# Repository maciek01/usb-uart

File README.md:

# usb-uart

first prototype for usb->uart board with FTDI 232rl

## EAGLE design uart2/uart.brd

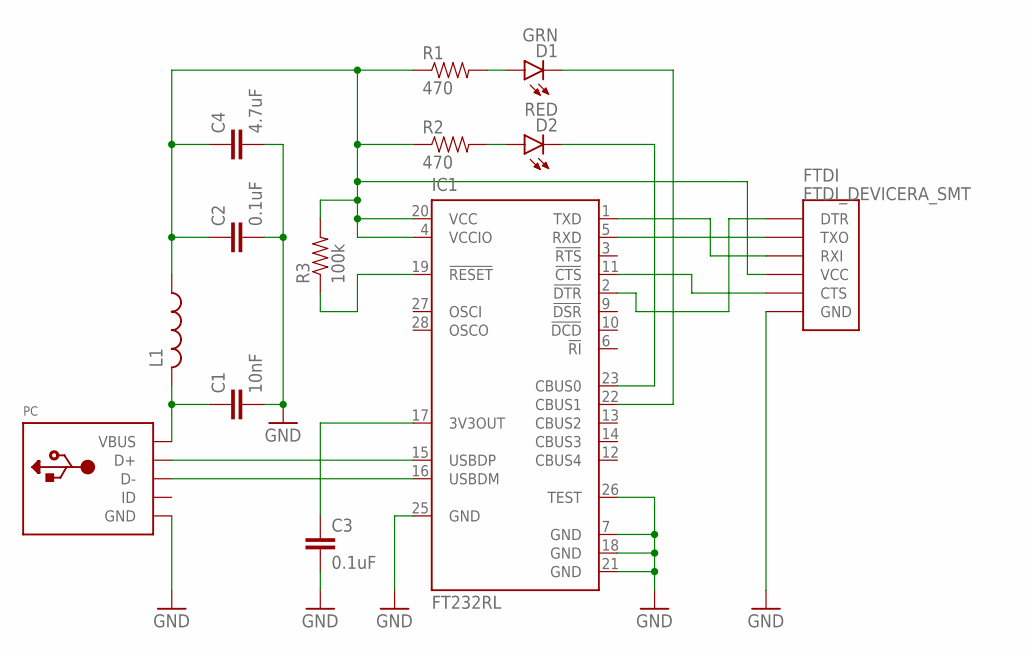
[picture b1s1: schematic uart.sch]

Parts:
C1: 10nF; 0603-CAP; MPN C0603C103J1RACTU
C2, C3: 0.1uF; 0603-CAP; MPN C0603C104K4RAC7081
C4: 4.7uF; 0603-CAP; MPN 0603F475Z100CT
D1: GRN; LED-0603; MPN HSME-C191
D2: RED; LED-0603; MPN HSMC-C120
FTDI: FTDI_DEVICERA_SMT; FTDI_DEVICE_RA_SMT
IC1: FT232RL; SSOP28; MPN FT232RL-REEL
L1: L-USL2012C; L2012C; MPN 744052180
PC: USBMINIB; USB-MINIB; MPN MUSB-B5-S-RA-TSMT-CS1
R1, R2: 470; 0603-RES; MPN ERJ-P03F4700V
R3: 100k; 0603-RES; MPN ERA-3AEB104V

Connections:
GND: C1.2, C2.2, C3.2, C4.2, FTDI.6 (GND), IC1.7 (GND), IC1.18 (GND), IC1.21 (GND), IC1.25 (GND), IC1.26 (TEST), PC.GND
unnamed: IC1.15 (USBDP), PC.D+
unnamed: IC1.16 (USBDM), PC.D-
unnamed: C3.1, IC1.17 (3V3OUT)
unnamed: FTDI.5 (CTS), IC1.11 (!CTS)
unnamed: FTDI.1 (DTR), IC1.2 (!DTR)
unnamed: IC1.19 (!RESET), R3.1
unnamed: C2.1, C4.1, FTDI.4 (VCC), IC1.4 (VCCIO), IC1.20 (VCC), L1.1, R1.1, R2.1, R3.2
unnamed: D2.C, IC1.23 (CBUS0)
unnamed: D2.A, R2.2
unnamed: D1.A, R1.2
unnamed: D1.C, IC1.22 (CBUS1)
unnamed: C1.1, L1.2, PC.VBUS
unnamed: FTDI.3 (RXI), IC1.1 (TXD)
unnamed: FTDI.2 (TXO), IC1.5 (RXD)

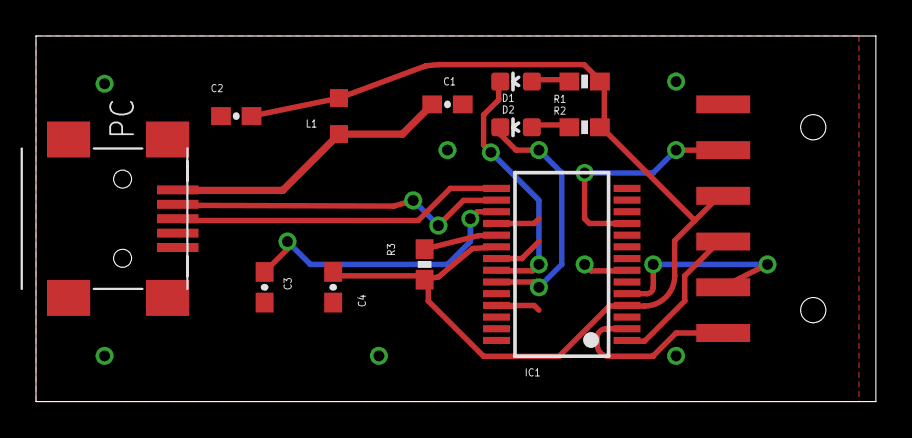
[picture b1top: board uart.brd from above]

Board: 2 copper layers, 46.7 x 20.3 mm, 13 parts (0 on the bottom side), 15 nets.

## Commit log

2016-09-28 remove gerbers.zip
2016-09-28 remove a file
2016-09-28 remove backups from repo
2016-09-28 remove unneeded files
2016-09-28 windows test
2016-10-22 added uart v2
2016-10-22 ignore file

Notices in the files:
parts and their libraries:
SparkFun-Capacitors: Licensing: Creative Commons ShareAlike 4.0 International - https://creativecommons.org/licenses/by-sa/4.0
